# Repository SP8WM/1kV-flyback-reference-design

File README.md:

# 1kV-flyback-reference-design
it's a design note from Analog DN1047. I think it might be modified for 1.5kV output with some kind of regulation and different kind of this rare switching transformer

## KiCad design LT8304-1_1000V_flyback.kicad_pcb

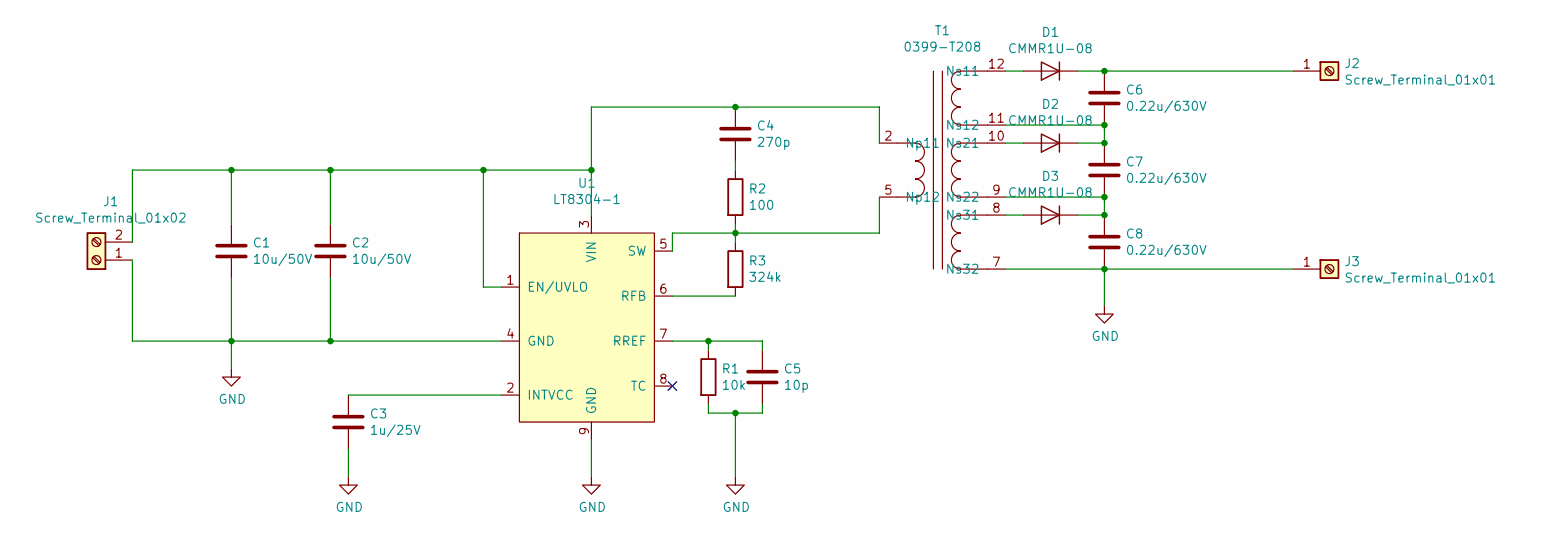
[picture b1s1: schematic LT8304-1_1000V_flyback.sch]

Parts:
C1, C2: 10u/50V; C_1210_3225Metric_Pad1.42x2.65mm_HandSolder
C3: 1u/25V; C_1206_3216Metric_Pad1.42x1.75mm_HandSolder
C4: 270p; C_0603_1608Metric_Pad1.05x0.95mm_HandSolder
C5: 10p; C_0603_1608Metric_Pad1.05x0.95mm_HandSolder
C6, C7, C8: 0.22u/630V; C_1812_4532Metric_Pad1.30x3.40mm_HandSolder
D1, D2, D3: CMMR1U-08; D_SOD-123F
J1: Screw_Terminal_01x02; PinHeader_1x02_P2.54mm_Vertical
J2, J3: Screw_Terminal_01x01; PinHeader_1x01_P2.54mm_Vertical
R1: 10k; R_0603_1608Metric_Pad1.05x0.95mm_HandSolder
R2: 100; R_1206_3216Metric_Pad1.42x1.75mm_HandSolder
R3: 324k; R_0805_2012Metric_Pad1.15x1.40mm_HandSolder
T1: 0399-T208
U1: LT8304-1; SOIC-8-1EP_3.9x4.9mm_P1.27mm_EP2.35x2.35mm

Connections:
GND: C1.2, C2.2, C3.2, C5.2, C8.2, J1.1, J3.1, R1.2, T1.7 (Ns32), U1.4 (GND), U1.9 (GND)
unnamed: C1.1, C2.1, C4.1, J1.2, T1.2 (Np11), U1.1 (EN/UVLO), U1.3 (VIN)
unnamed: C3.1, U1.2 (INTVCC)
unnamed: C4.2, R2.1
unnamed: C5.1, R1.1, U1.7 (RREF)
unnamed: C6.1, D1.1 (K), J2.1
unnamed: C6.2, C7.1, D2.1 (K), T1.11 (Ns12)
unnamed: C7.2, C8.1, D3.1 (K), T1.9 (Ns22)
unnamed: D1.2 (A), T1.12 (Ns11)
unnamed: D2.2 (A), T1.10 (Ns21)
unnamed: D3.2 (A), T1.8 (Ns31)
unnamed: R2.2, R3.1, T1.5 (Np12), U1.5 (SW)
unnamed: R3.2, U1.6 (RFB)

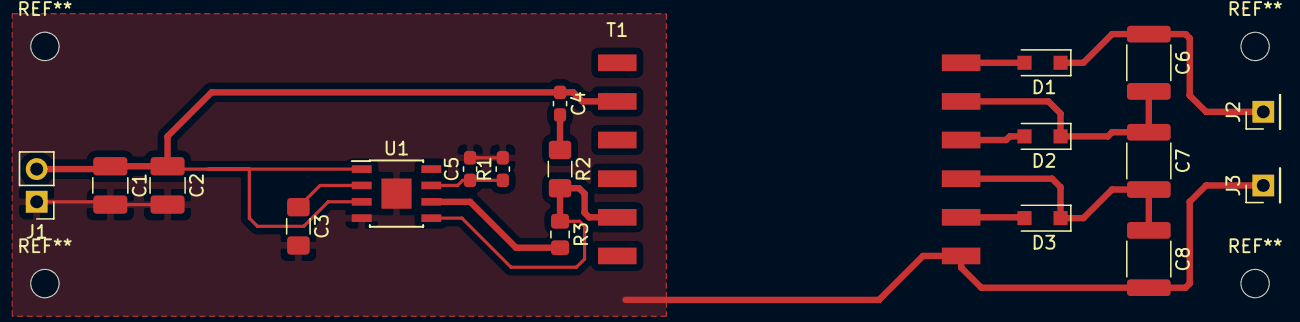
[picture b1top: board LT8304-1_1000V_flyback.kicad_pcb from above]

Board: 2 copper layers, 19 parts (0 on the bottom side), 13 nets.
